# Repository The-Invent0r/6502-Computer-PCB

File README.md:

# 6502-Computer-PCB

DISCLAIMER: I DELETED ALL OF THE CONNECTIONS FOR GRANT SEARLE'S VIDEO+KEYBOARD INTERFACE BEFORE UPLOADING THE FILES. IF YOU WANT TO ADD IN THE VIDEO+KEYBOARD INTERFACE PLEASE TAKE A LOOK AT HIS WEBSITE (http://searle.x10host.com/MonitorKeyboard/index.html) AND FOLLOW THE DIRECTIONS ON THERE. IT MIGHT BE WORTH IT TO PROTOTYPE THE INTERFACE ON BREADBOARDS FIRST.

I made this Modified version of Ben Eater's 6502 computer PCB and decided instead of adding a VGA video card, I wanted to connect this to a CRT monitor using a composite video cable. 
I decided to add in a 6551 ACIA (Asyncronous Communications Interface Adapter) to give the computer serial I/O capabilites. I then found Grant Searle's video+keyboard interface and decided to incorporate that into my design. 
The only issue was that my 6551 was sending and receiving data at 19200 baud, and the video+keyboard interface was running at 115200 baud. Luckily it was an easy fix to go into the software and update the USART_BAUD variable from 115200u1 to 19200u1. 
However, before uploading the code I changed the fuse bytes to ensure that the 2 AVR chips were running at the correct crystal oscillator frequencies. 
To upload the code for the keyboard chip I used WinAVR. I found that before uploading the keyboard interface code, I needed to change the file name to main.c and I also had to create my own makefile for the atmega328p. 
For the video chip I decided to use the .hex file, and burn that directly into the other atmega328p using the command line. 
When I first prototyped this circuit on breadboards I had a lot of issues which I later discovered were caused by using a low quality breadboard. So if all off your connections and software are correct, try using a more expensive but higher quality BB830 breadboard.
When you first connect the circuit to an LCD monitor or CRT monitor you should see a cursor blinking. In order to conduct a loopback test of the circuit, simply connect the Rx pin to the Tx pin on the keyboard chip, then connect the PS2 keyboard and start typing. If it works then you'll see the correct characters on the screen.

I also made a YouTube video briefly documenting my progress and demonstrating the workings of the computer. (https://youtu.be/8I7XNCFC5iU)

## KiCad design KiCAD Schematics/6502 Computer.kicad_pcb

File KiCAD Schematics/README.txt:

I've removed all the connections between the two Atmega328p chips and the 74HC166 chip since the design is copyrighted. But all the connections can be found on Grant Searle's website (http://searle.x10host.com/MonitorKeyboard/index.html) along with instructions on how to connect them to your specific display.

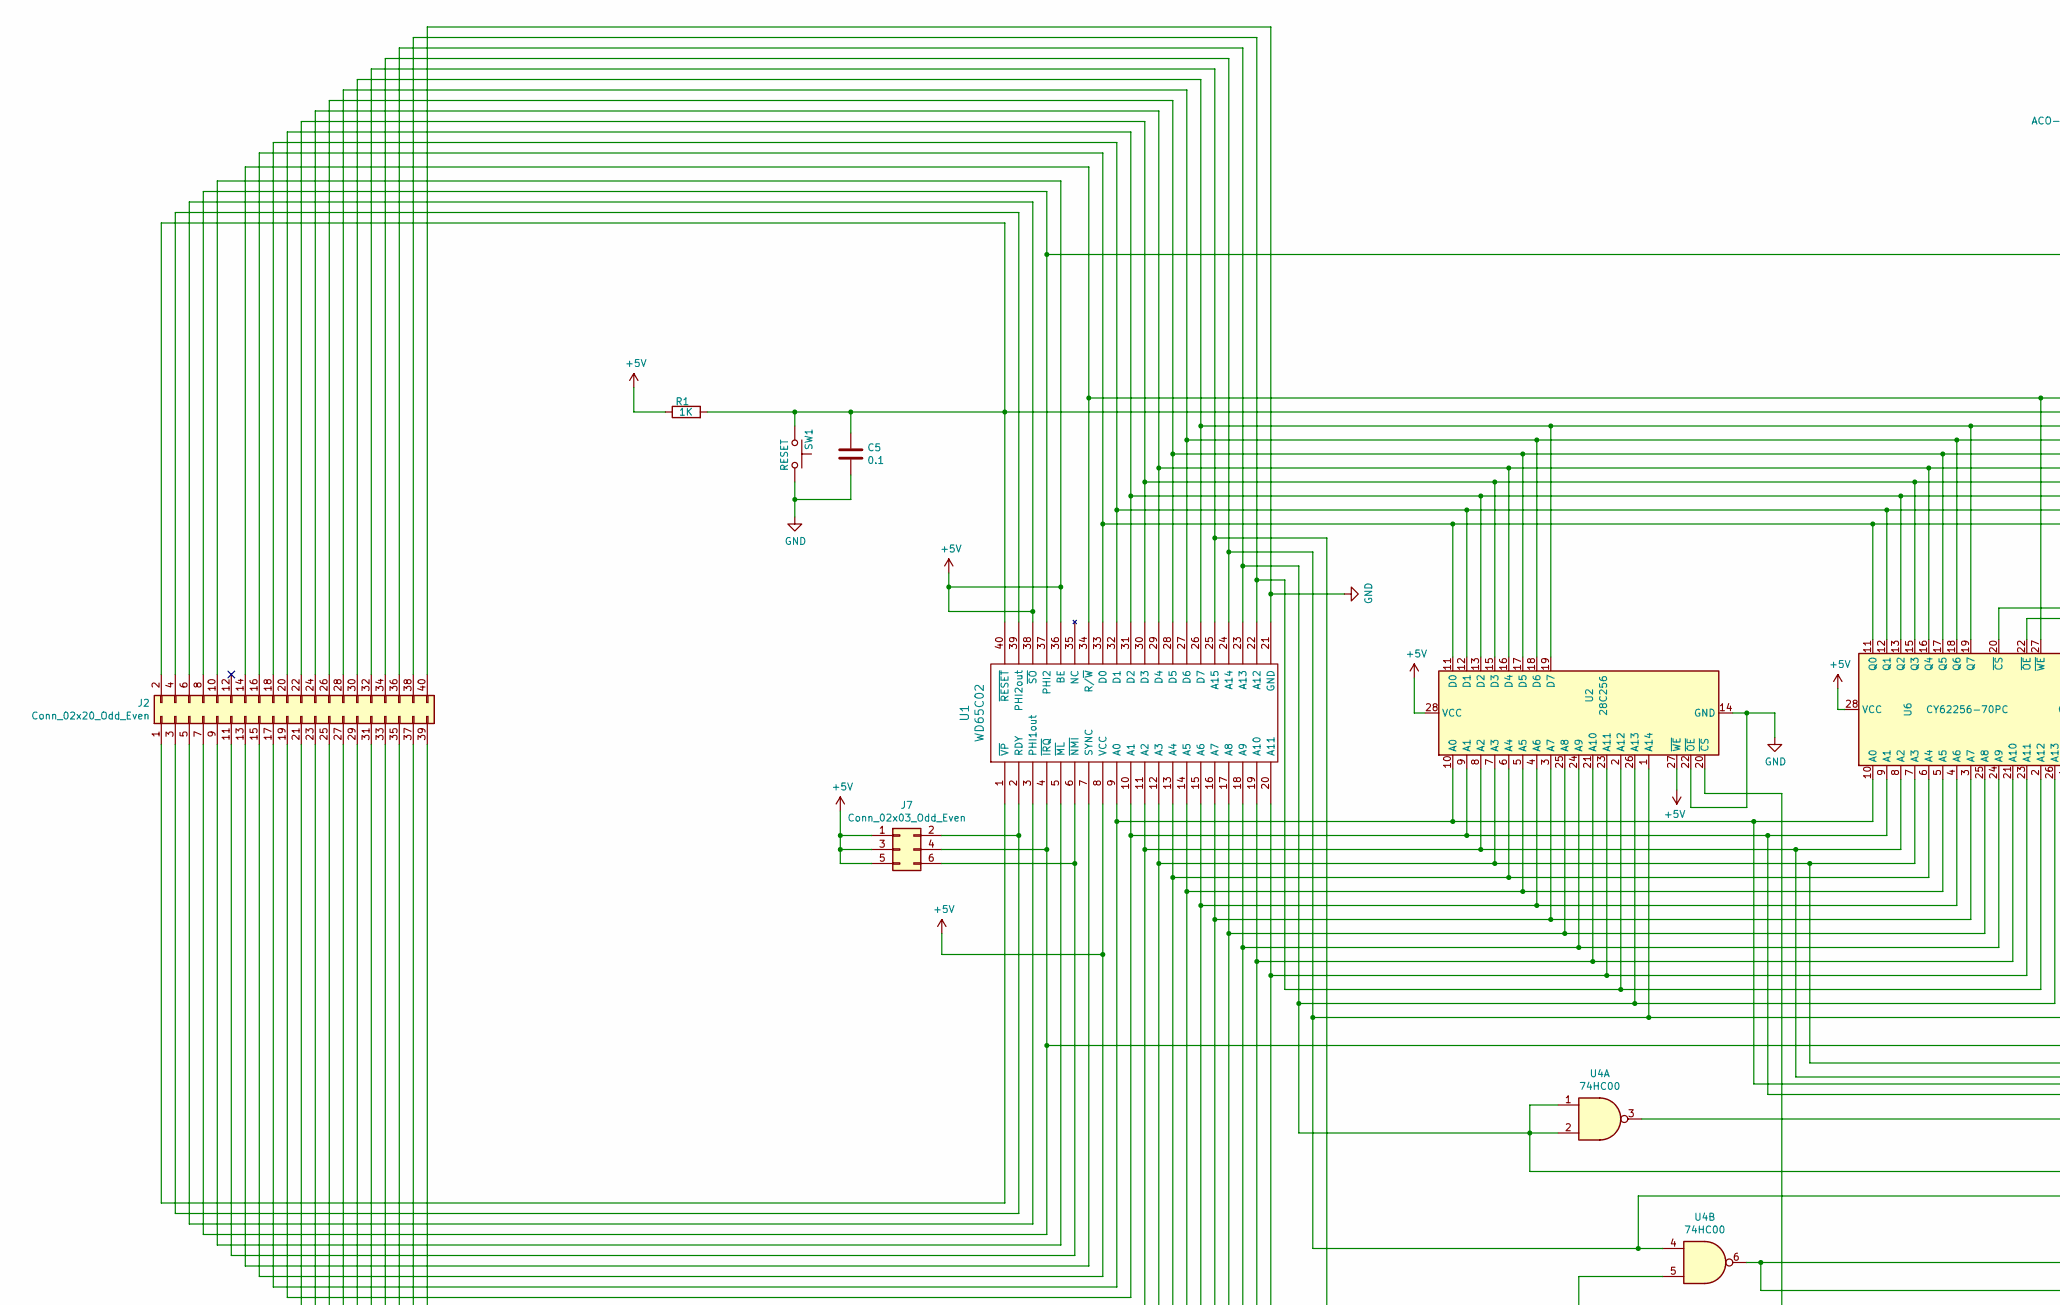
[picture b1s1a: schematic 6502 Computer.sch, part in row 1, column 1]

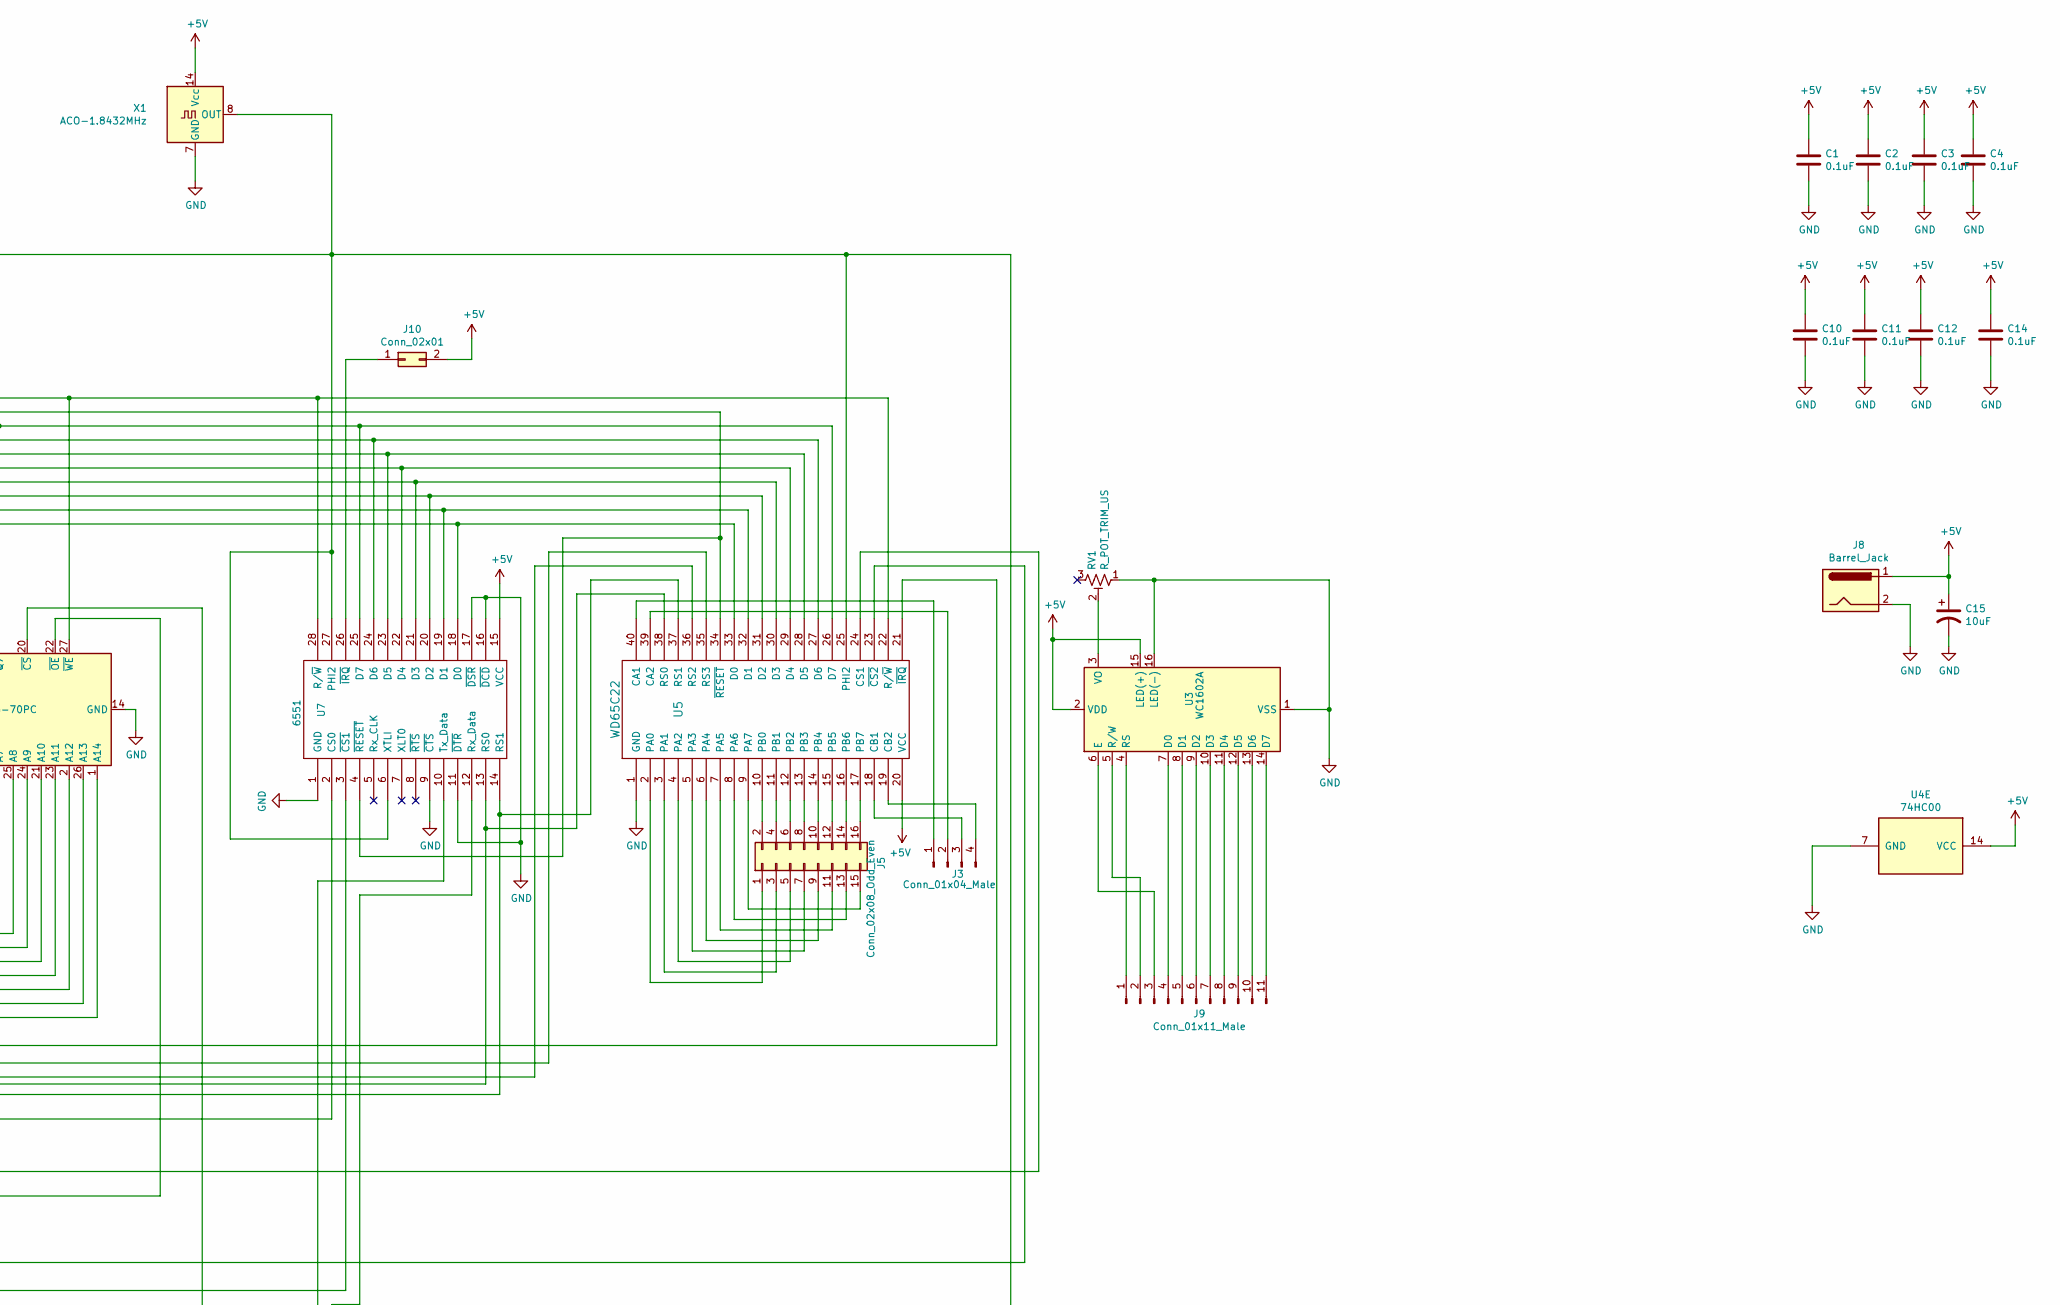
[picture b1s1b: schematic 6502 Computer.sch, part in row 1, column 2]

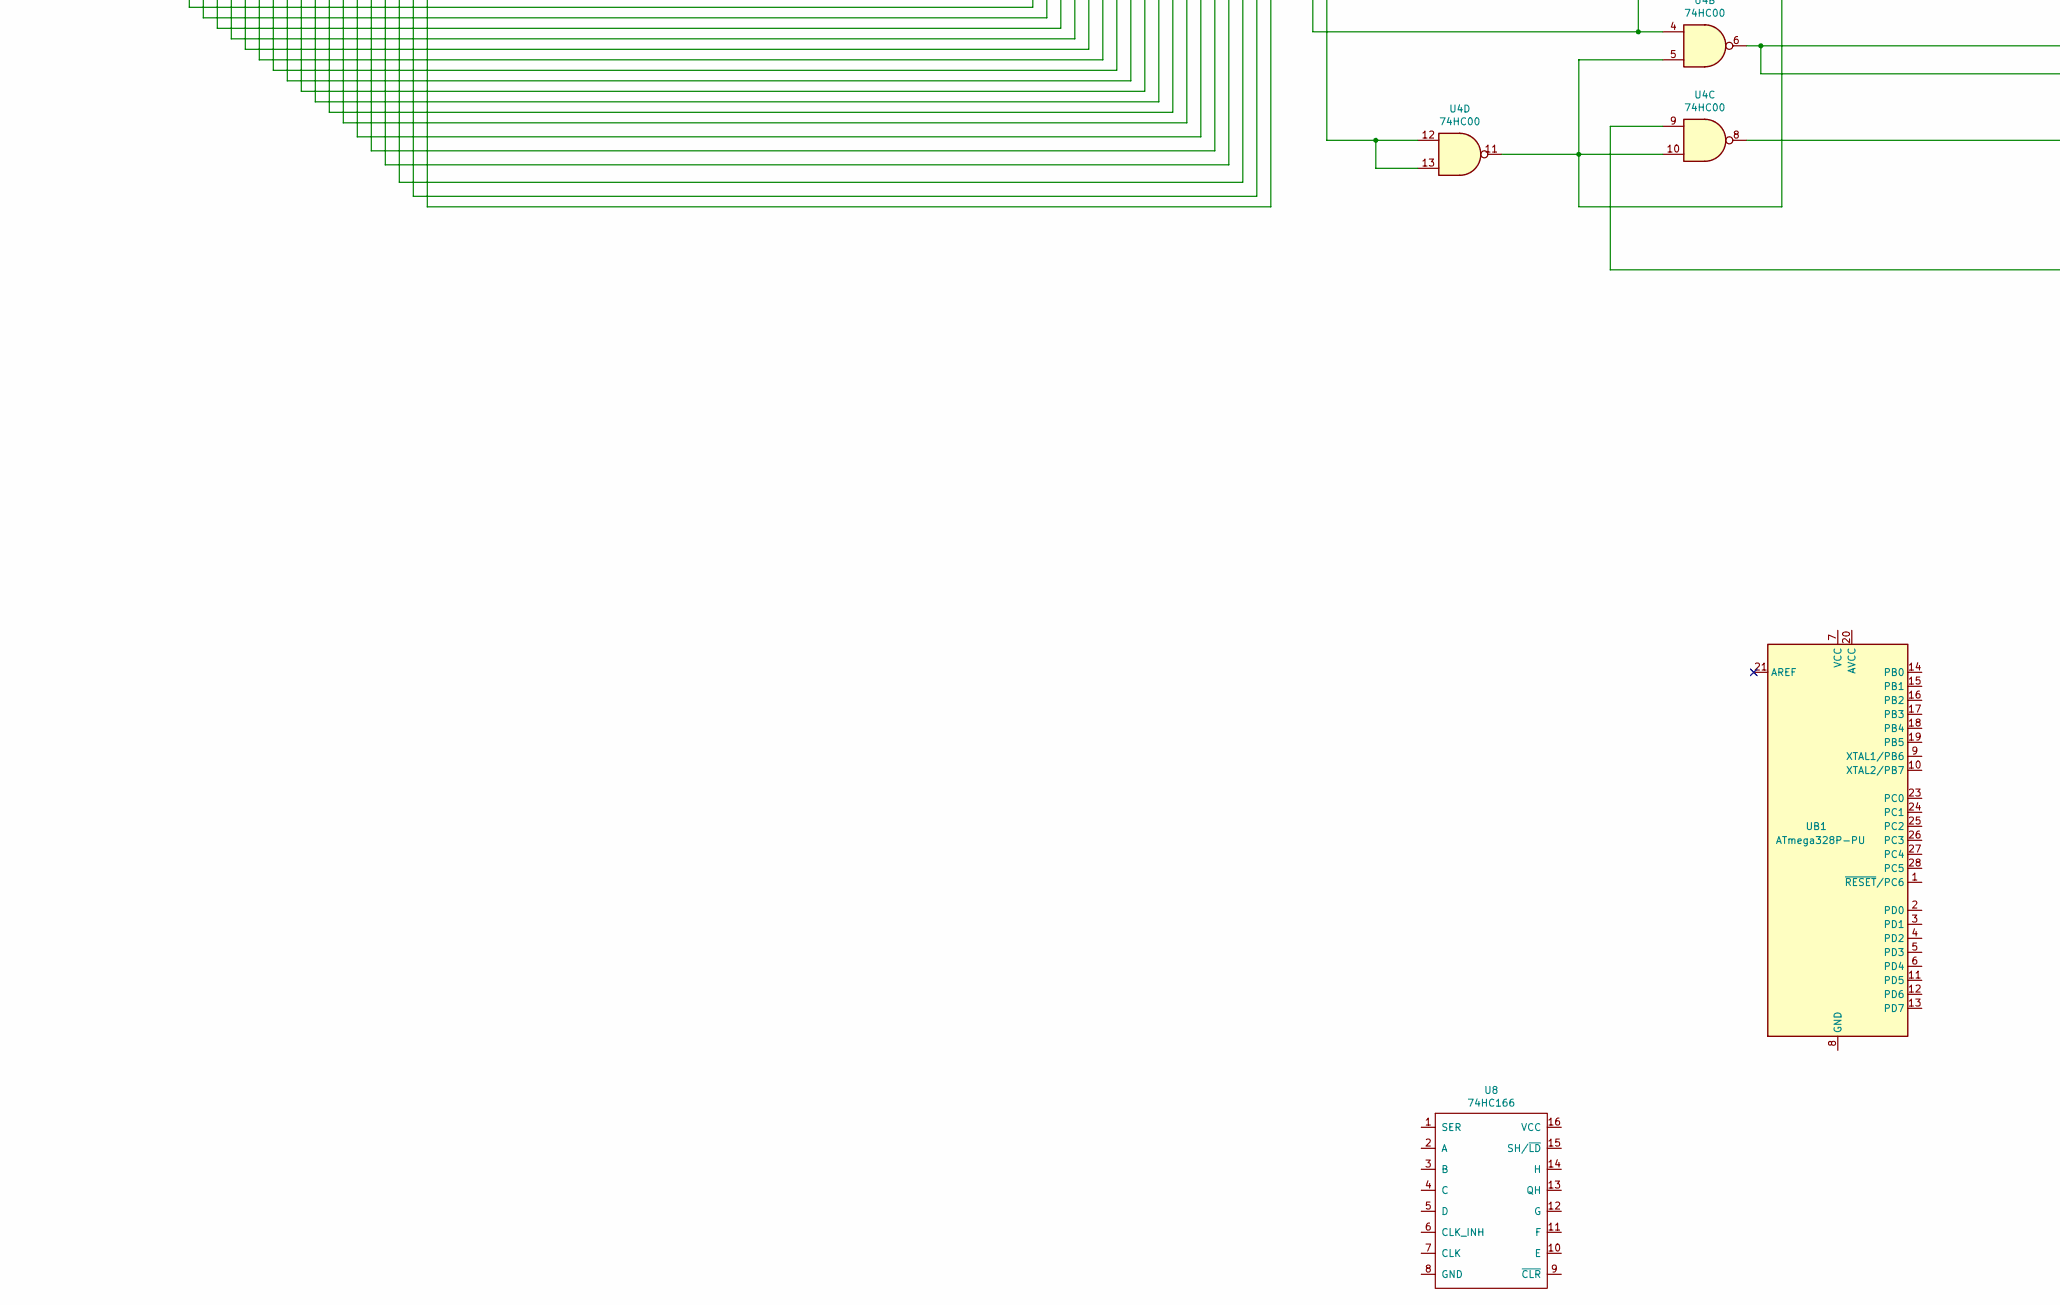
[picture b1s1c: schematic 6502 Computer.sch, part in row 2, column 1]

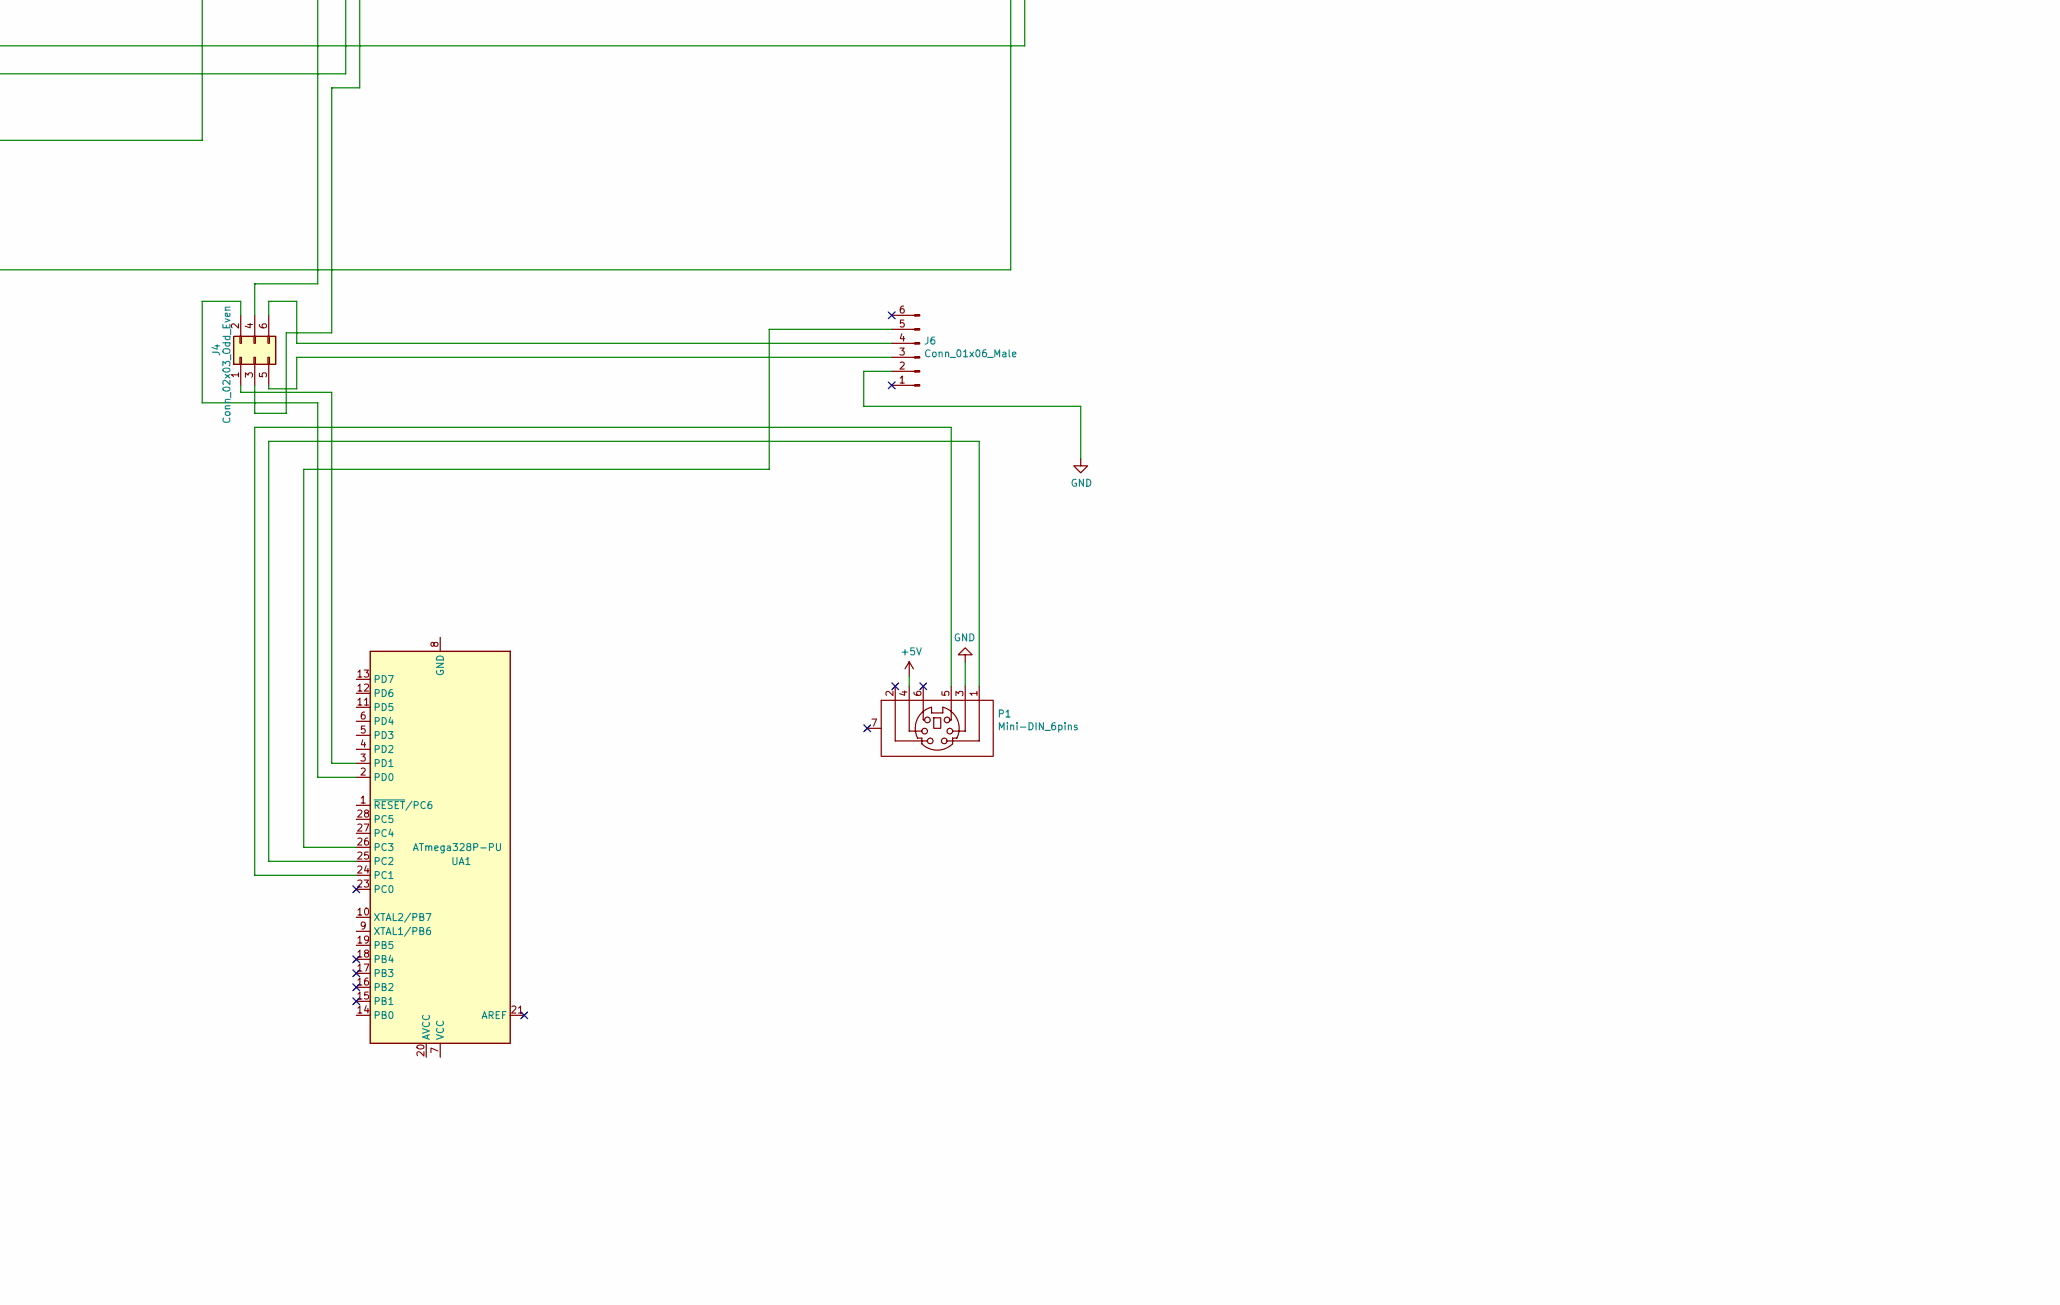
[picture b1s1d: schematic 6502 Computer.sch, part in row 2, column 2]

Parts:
C1, C2, C3, C4, C10, C11, C12, C14: 0.1uF; C_Disc_D4.3mm_W1.9mm_P5.00mm
C5: 0.1; C_Disc_D4.3mm_W1.9mm_P5.00mm
C15: 10uF; CP_Radial_D5.0mm_P2.00mm
J2: Conn_02x20_Odd_Even; PinHeader_2x20_P2.54mm_Vertical
J3: Conn_01x04_Male; PinHeader_1x04_P2.54mm_Vertical
J4, J7: Conn_02x03_Odd_Even; PinHeader_2x03_P2.54mm_Vertical
J5: Conn_02x08_Odd_Even; PinHeader_2x08_P2.54mm_Vertical
J6: Conn_01x06_Male; PinHeader_1x06_P2.54mm_Horizontal
J8: Barrel_Jack; BarrelJack_CUI_PJ-063AH_Horizontal
J9: Conn_01x11_Male; PinHeader_1x11_P2.54mm_Vertical
J10: Conn_02x01; PinHeader_2x01_P2.54mm_Vertical
P1: Mini-DIN_6pins; Connector_Mini-DIN_Female_6Pin_2rows
R1: 1K; R_Axial_DIN0207_L6.3mm_D2.5mm_P7.62mm_Horizontal
RV1: R_POT_TRIM_US; Potentiometer_Bourns_3386C_Horizontal
SW1: RESET; SW_PUSH_6mm_H5mm
U1: WD65C02; DIP-40_W15.24mm_Socket_LongPads
U2: 28C256; DIP-28_W15.24mm_Socket_LongPads
U3: WC1602A
U4: 74HC00; DIP-14_W7.62mm_Socket_LongPads
U5: WD65C22; DIP-40_W15.24mm_Socket_LongPads
U6: CY62256-70PC; DIP-28_W15.24mm_Socket_LongPads
U7: 6551; DIP-28_W15.24mm_Socket_LongPads
U8: 74HC166; DIP-16_W7.62mm_Socket_LongPads
UA1: ATmega328P-PU; DIP-28_W7.62mm_Socket_LongPads
UB1: ATmega328P-PU; DIP-28_W7.62mm_Socket_LongPads
X1: ACO-1.8432MHz; Oscillator_DIP-14

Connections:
+5V: C1.1, C2.1, C3.1, C4.1, C10.1, C11.1, C12.1, C14.1, C15.1, J2.6, J2.10, J2.15, J7.1, J7.3, J7.5, J8.1, J10.2, P1.4, R1.1, U1.8 (VCC), U1.36 (BE), U1.38 (~SO), U2.27 (~WE), U2.28 (VCC), U3.2 (VDD), U3.15 (LED(+)), U4.14 (VCC), U5.20 (VCC), U6.28 (VCC), U7.15 (VCC), X1.14 (Vcc)
GND: C1.2, C2.2, C3.2, C4.2, C5.2, C10.2, C11.2, C12.2, C14.2, C15.2, J2.40, J6.2, J8.2, P1.3, RV1.1, SW1.2, U1.21 (GND), U2.14 (GND), U2.22 (~OE), U3.1 (VSS), U3.16 (LED(-)), U4.7 (GND), U5.1 (GND), U6.14 (GND), U7.1 (GND), U7.9 (~CTS), U7.11 (~DTR), U7.16 (~DCD), U7.17 (~DSR), X1.7 (GND)
unnamed: C5.1, J2.2, R1.2, SW1.1, U1.40 (~RESET), U5.34 (~RESET), U7.4 (~RESET)
unnamed: J2.1, U1.1 (~VP)
unnamed: J2.3, J7.2, U1.2 (RDY)
unnamed: J2.4, U1.39 (PHI2out)
unnamed: J2.5, U1.3 (PHI1out)
unnamed: J2.7, J7.4, U1.4 (~IRQ), U5.21 (~IRQ)
unnamed: J2.8, U1.37 (PHI2), U4.9, U5.25 (PHI2), U7.6 (XTLI), U7.27 (PHI2), X1.8 (OUT)
unnamed: J2.9, U1.5 (~ML)
unnamed: J2.11, J7.6, U1.6 (~NMI)
unnamed: J2.13, U1.7 (SYNC)
unnamed: J2.14, U1.34 (R/~W), U5.22 (R/~W), U6.27 (~WE), U7.28 (R/~W)
unnamed: J2.16, U1.33 (D0), U2.11 (D0), U5.33 (D0), U6.11 (Q0), U7.18 (D0)
unnamed: J2.17, U1.9 (A0), U2.10 (A0), U5.38 (RS0), U6.10 (A0), U7.13 (RS0)
unnamed: J2.18, U1.32 (D1), U2.12 (D1), U5.32 (D1), U6.12 (Q1), U7.19 (D1)
unnamed: J2.19, U1.10 (A1), U2.9 (A1), U5.37 (RS1), U6.9 (A1), U7.14 (RS1)
unnamed: J2.20, U1.31 (D2), U2.13 (D2), U5.31 (D2), U6.13 (Q2), U7.20 (D2)
unnamed: J2.21, U1.11 (A2), U2.8 (A2), U5.36 (RS2), U6.8 (A2)
unnamed: J2.22, U1.30 (D3), U2.15 (D3), U5.30 (D3), U6.15 (Q3), U7.21 (D3)
unnamed: J2.23, U1.12 (A3), U2.7 (A3), U5.35 (RS3), U6.7 (A3)
unnamed: J2.24, U1.29 (D4), U2.16 (D4), U5.29 (D4), U6.16 (Q4), U7.22 (D4)
unnamed: J2.25, U1.13 (A4), U2.6 (A4), U6.6 (A4)
unnamed: J2.26, U1.28 (D5), U2.17 (D5), U5.28 (D5), U6.17 (Q5), U7.23 (D5)
unnamed: J2.27, U1.14 (A5), U2.5 (A5), U6.5 (A5)
unnamed: J2.28, U1.27 (D6), U2.18 (D6), U5.27 (D6), U6.18 (Q6), U7.24 (D6)
unnamed: J2.29, U1.15 (A6), U2.4 (A6), U6.4 (A6)
unnamed: J2.30, U1.26 (D7), U2.19 (D7), U5.26 (D7), U6.19 (Q7), U7.25 (D7)
unnamed: J2.31, U1.16 (A7), U2.3 (A7), U6.3 (A7)
unnamed: J2.32, U1.25 (A15), U4.12, U4.13
unnamed: J2.33, U1.17 (A8), U2.25 (A8), U6.25 (A8)
unnamed: J2.34, U1.24 (A14), U2.1 (A14), U4.4, U6.1 (A14), U6.22 (~OE)
unnamed: J2.35, U1.18 (A9), U2.24 (A9), U6.24 (A9)
unnamed: J2.36, U1.23 (A13), U2.26 (A13), U4.1, U4.2, U5.24 (CS1), U6.26 (A13)
unnamed: J2.37, U1.19 (A10), U2.21 (A10), U6.21 (A10)
unnamed: J2.38, U1.22 (A12), U2.2 (A12), U6.2 (A12)
unnamed: J2.39, U1.20 (A11), U2.23 (A11), U6.23 (A11)
unnamed: J3.1, U5.40 (CA1)
unnamed: J3.2, U5.39 (CA2)
unnamed: J3.3, U5.18 (CB1)
unnamed: J3.4, U5.19 (CB2)
unnamed: J4.1, UA1.3 (PD1)
unnamed: J4.2, UA1.2 (PD0)
unnamed: J4.3, U7.12 (Rx_Data)
unnamed: J4.4, U7.10 (Tx_Data)
unnamed: J4.5, J6.3
unnamed: J4.6, J6.4
unnamed: J5.1, U5.2 (PA0)
unnamed: J5.2, U5.10 (PB0)
unnamed: J5.3, U5.3 (PA1)
unnamed: J5.4, U5.11 (PB1)
unnamed: J5.5, U5.4 (PA2)
unnamed: J5.6, U5.12 (PB2)
unnamed: J5.7, U5.5 (PA3)
unnamed: J5.8, U5.13 (PB3)
unnamed: J5.9, U5.6 (PA4)
unnamed: J5.10, U5.14 (PB4)
unnamed: J5.11, U5.7 (PA5)
unnamed: J5.12, U5.15 (PB5)
unnamed: J5.13, U5.8 (PA6)
unnamed: J5.14, U5.16 (PB6)
unnamed: J5.15, U5.9 (PA7)
unnamed: J5.16, U5.17 (PB7)
unnamed: J6.5, UA1.26 (PC3)
unnamed: J9.1, U3.4 (RS)
unnamed: J9.2, U3.5 (R/W)
unnamed: J9.3, U3.6 (E)
unnamed: J9.4, U3.7 (D0)
unnamed: J9.5, U3.8 (D1)
unnamed: J9.6, U3.9 (D2)
unnamed: J9.7, U3.10 (D3)
unnamed: J9.8, U3.11 (D4)
unnamed: J9.9, U3.12 (D5)
unnamed: J9.10, U3.13 (D6)
unnamed: J9.11, U3.14 (D7)
unnamed: J10.1, U7.26 (~IRQ)
unnamed: P1.1, UA1.25 (PC2)
unnamed: P1.5, UA1.24 (PC1)
unnamed: RV1.2, U3.3 (VO)
unnamed: U2.20 (~CS), U4.5, U4.10, U4.11
unnamed: U4.3, U7.2 (CS0)
unnamed: U4.6, U5.23 (~CS2), U7.3 (~CS1)
unnamed: U4.8, U6.20 (~CS)
unnamed: UA1.8 (GND), UA1.22 (GND)
unnamed: UB1.8 (GND), UB1.22 (GND)

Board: 2 copper layers, 34 parts (0 on the bottom side), 85 nets, no tracks yet.

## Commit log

2022-10-08 Rename ReadMe.txt to README.txt
